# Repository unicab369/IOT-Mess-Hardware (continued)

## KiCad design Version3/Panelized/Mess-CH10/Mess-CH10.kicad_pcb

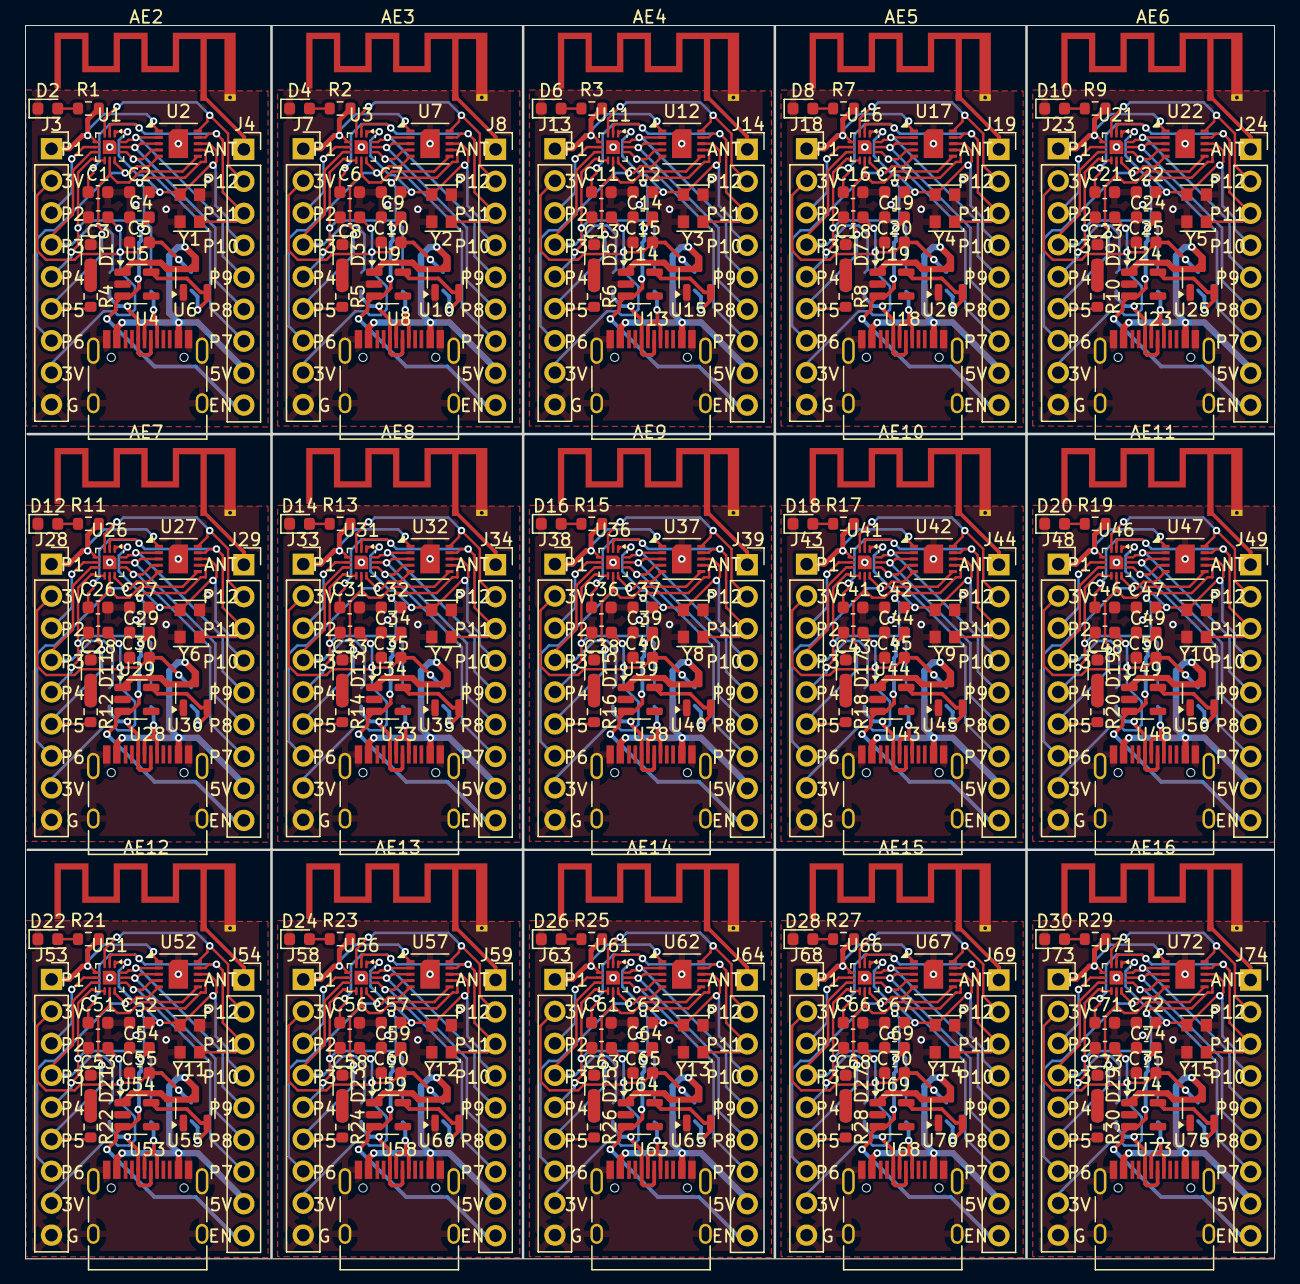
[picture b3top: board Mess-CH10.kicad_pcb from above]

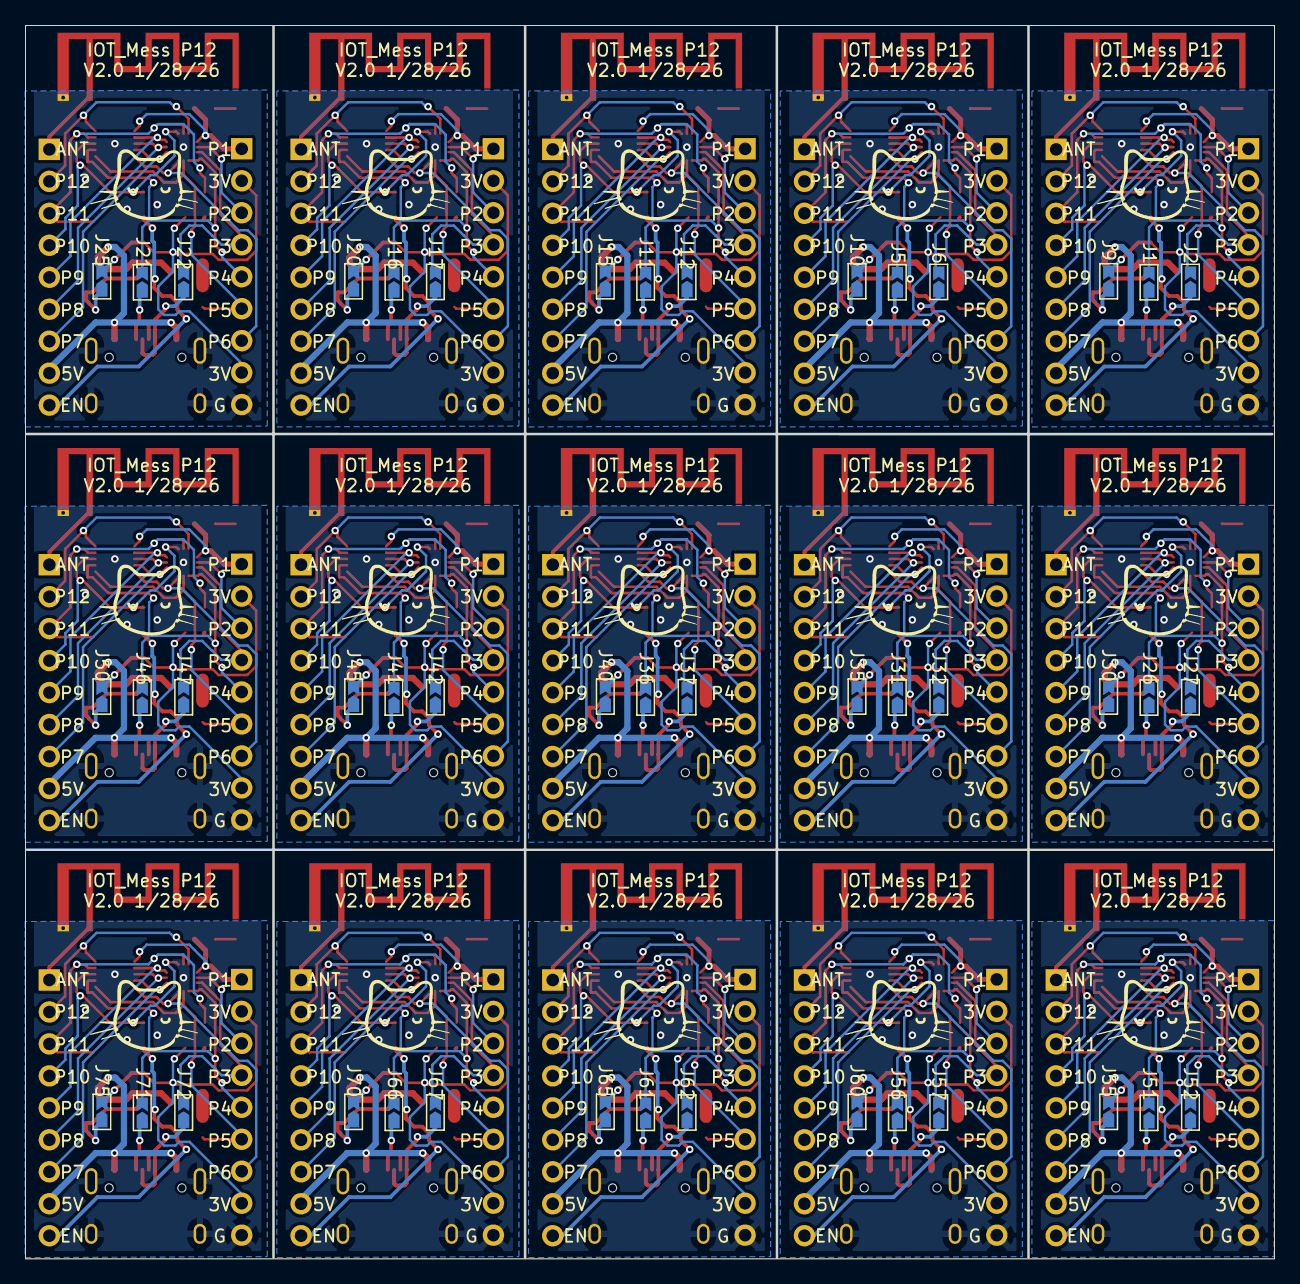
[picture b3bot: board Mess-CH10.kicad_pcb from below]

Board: 2 copper layers, 99.2 x 98.0 mm, 315 parts (45 on the bottom side), 22 nets.

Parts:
AE2, AE3, AE4, AE5, AE6, AE7, AE8, AE9, AE10, AE11, AE12, AE13, AE14, AE15, AE16: Antenna_Shield; Texas_SWRA117D_2.4GHz_Left
C1, C2, C6, C7, C11, C12, C16, C17, C21, C22, C26, C27, C31, C32, C36, C37, C41, C42, C46, C47, C51, C52, C56, C57, C61, C62, C66, C67, C71, C72: 12-25pF; C_0603_1608Metric
C3, C8, C13, C18, C23, C28, C33, C38, C43, C48, C53, C58, C63, C68, C73: 10u; C_0603_1608Metric
C4, C5, C9, C10, C14, C15, C19, C20, C24, C25, C29, C30, C34, C35, C39, C40, C44, C45, C49, C50, C54, C55, C59, C60, C64, C65, C69, C70, C74, C75: 1u; C_0603_1608Metric
D1, D2, D3, D4, D5, D6, D7, D8, D9, D10, D11, D12, D13, D14, D15, D16, D17, D18, D19, D20, D21, D22, D23, D24, D25, D26, D27, D28, D29, D30: LED; LED_0603_1608Metric
J1, J2, J5, J6, J9, J10, J11, J12, J15, J16, J17, J20, J21, J22, J25, J26, J27, J30, J31, J32, J35, J36, J37, J40, J41, J42, J45, J46, J47, J50, J51, J52, J55, J56, J57, J60, J61, J62, J65, J66, J67, J70, J71, J72, J75: Jumper_2; Jumper-triangle
J3, J4, J7, J8, J13, J14, J18, J19, J23, J24, J28, J29, J33, J34, J38, J39, J43, J44, J48, J49, J53, J54, J58, J59, J63, J64, J68, J69, J73, J74: Conn_01x09_Pin; PinSocket_1x09_P2.54mm_Vertical
R1, R2, R3, R4, R5, R6, R7, R8, R9, R10, R11, R12, R13, R14, R15, R16, R17, R18, R19, R20, R21, R22, R23, R24, R25, R26, R27, R28, R29, R30: R; R_0603_1608Metric
U1, U3, U11, U16, U21, U26, U31, U36, U41, U46, U51, U56, U61, U66, U71: UQFN-12-1EP_2x2mm_P0.4mm_EP1.1x1.1mm
U2, U7, U12, U17, U22, U27, U32, U37, U42, U47, U52, U57, U62, U67, U72: CH57xQ_QFN10x3; DFN10x3
U4, U8, U13, U18, U23, U28, U33, U38, U43, U48, U53, U58, U63, U68, U73: USB_C_Receptacle_USB2.0_16P; USB_C_Receptacle_HRO_TYPE-C-31-M-12
U5, U9, U14, U19, U24, U29, U34, U39, U44, U49, U54, U59, U64, U69, U74: ME6211C33M5; SOT-23-5
U6, U10, U15, U20, U25, U30, U35, U40, U45, U50, U55, U60, U65, U70, U75: XC6206PxxxMR; SOT-23-3
Y1, Y2, Y3, Y4, Y5, Y6, Y7, Y8, Y9, Y10, Y11, Y12, Y13, Y14, Y15: XO32; Oscillator_SMD_EuroQuartz_XO32-4Pin_3.2x2.5mm

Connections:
5V: J4.8, J8.8, J14.8, J19.8, J24.8, J29.8, J34.8, J39.8, J44.8, J49.8, J54.8, J59.8, J64.8, J69.8, J74.8, U4.A4 (VBUS), U4.A9 (VBUS), U4.B4 (VBUS), U4.B9 (VBUS), U5.1 (V_{IN}), U6.3 (VI), U8.A4 (VBUS), U8.A9 (VBUS), U8.B4 (VBUS), U8.B9 (VBUS), U9.1 (V_{IN}), U10.3 (VI), U13.A4 (VBUS), U13.A9 (VBUS), U13.B4 (VBUS), U13.B9 (VBUS), U14.1 (V_{IN}), U15.3 (VI), U18.A4 (VBUS), U18.A9 (VBUS), U18.B4 (VBUS), U18.B9 (VBUS), U19.1 (V_{IN}), U20.3 (VI), U23.A4 (VBUS), U23.A9 (VBUS), U23.B4 (VBUS), U23.B9 (VBUS), U24.1 (V_{IN}), U25.3 (VI), U28.A4 (VBUS), U28.A9 (VBUS), U28.B4 (VBUS), U28.B9 (VBUS), U29.1 (V_{IN}), U30.3 (VI), U33.A4 (VBUS), U33.A9 (VBUS), U33.B4 (VBUS), U33.B9 (VBUS), U34.1 (V_{IN}), U35.3 (VI), U38.A4 (VBUS), U38.A9 (VBUS), U38.B4 (VBUS), U38.B9 (VBUS), U39.1 (V_{IN}), U40.3 (VI), U43.A4 (VBUS), U43.A9 (VBUS), U43.B4 (VBUS), U43.B9 (VBUS), U44.1 (V_{IN}), U45.3 (VI), U48.A4 (VBUS), U48.A9 (VBUS), U48.B4 (VBUS), U48.B9 (VBUS), U49.1 (V_{IN}), U50.3 (VI), U53.A4 (VBUS), U53.A9 (VBUS), U53.B4 (VBUS), U53.B9 (VBUS), U54.1 (V_{IN}), U55.3 (VI), U58.A4 (VBUS), U58.A9 (VBUS), U58.B4 (VBUS), U58.B9 (VBUS), U59.1 (V_{IN}), U60.3 (VI), U63.A4 (VBUS), U63.A9 (VBUS), U63.B4 (VBUS), U63.B9 (VBUS), U64.1 (V_{IN}), U65.3 (VI), U68.A4 (VBUS), U68.A9 (VBUS), U68.B4 (VBUS), U68.B9 (VBUS), U69.1 (V_{IN}), U70.3 (VI), U73.A4 (VBUS), U73.A9 (VBUS), U73.B4 (VBUS), U73.B9 (VBUS), U74.1 (V_{IN}), U75.3 (VI)
+3.3V: C3.1, C5.1, C8.1, C10.1, C13.1, C15.1, C18.1, C20.1, C23.1, C25.1, C28.1, C30.1, C33.1, C35.1, C38.1, C40.1, C43.1, C45.1, C48.1, C50.1, C53.1, C55.1, C58.1, C60.1, C63.1, C65.1, C68.1, C70.1, C73.1, C75.1, J3.2, J3.8, J7.2, J7.8, J9.2 (B), J10.2 (B), J13.2, J13.8, J15.2 (B), J18.2, J18.8, J20.2 (B), J23.2, J23.8, J25.2 (B), J28.2, J28.8, J30.2 (B), J33.2, J33.8, J35.2 (B), J38.2, J38.8, J40.2 (B), J43.2, J43.8, J45.2 (B), J48.2, J48.8, J50.2 (B), J53.2, J53.8, J55.2 (B), J58.2, J58.8, J60.2 (B), J63.2, J63.8, J65.2 (B), J68.2, J68.8, J70.2 (B), J73.2, J73.8, J75.2 (B)
D+: J1.1 (A), J5.1 (A), J11.1 (A), J16.1 (A), J21.1 (A), J26.1 (A), J31.1 (A), J36.1 (A), J41.1 (A), J46.1 (A), J51.1 (A), J56.1 (A), J61.1 (A), J66.1 (A), J71.1 (A), U4.A6 (D+), U4.B6 (D+), U8.A6 (D+), U8.B6 (D+), U13.A6 (D+), U13.B6 (D+), U18.A6 (D+), U18.B6 (D+), U23.A6 (D+), U23.B6 (D+), U28.A6 (D+), U28.B6 (D+), U33.A6 (D+), U33.B6 (D+), U38.A6 (D+), U38.B6 (D+), U43.A6 (D+), U43.B6 (D+), U48.A6 (D+), U48.B6 (D+), U53.A6 (D+), U53.B6 (D+), U58.A6 (D+), U58.B6 (D+), U63.A6 (D+), U63.B6 (D+), U68.A6 (D+), U68.B6 (D+), U73.A6 (D+), U73.B6 (D+)
D-: J2.1 (A), J6.1 (A), J12.1 (A), J17.1 (A), J22.1 (A), J27.1 (A), J32.1 (A), J37.1 (A), J42.1 (A), J47.1 (A), J52.1 (A), J57.1 (A), J62.1 (A), J67.1 (A), J72.1 (A), U4.A7 (D-), U4.B7 (D-), U8.A7 (D-), U8.B7 (D-), U13.A7 (D-), U13.B7 (D-), U18.A7 (D-), U18.B7 (D-), U23.A7 (D-), U23.B7 (D-), U28.A7 (D-), U28.B7 (D-), U33.A7 (D-), U33.B7 (D-), U38.A7 (D-), U38.B7 (D-), U43.A7 (D-), U43.B7 (D-), U48.A7 (D-), U48.B7 (D-), U53.A7 (D-), U53.B7 (D-), U58.A7 (D-), U58.B7 (D-), U63.A7 (D-), U63.B7 (D-), U68.A7 (D-), U68.B7 (D-), U73.A7 (D-), U73.B7 (D-)
GND: AE2.2 (Shield), AE3.2 (Shield), AE4.2 (Shield), AE5.2 (Shield), AE6.2 (Shield), AE7.2 (Shield), AE8.2 (Shield), AE9.2 (Shield), AE10.2 (Shield), AE11.2 (Shield), AE12.2 (Shield), AE13.2 (Shield), AE14.2 (Shield), AE15.2 (Shield), AE16.2 (Shield), C1.2, C2.2, C3.2, C4.2, C5.2, C6.2, C7.2, C8.2, C9.2, C10.2, C11.2, C12.2, C13.2, C14.2, C15.2, C16.2, C17.2, C18.2, C19.2, C20.2, C21.2, C22.2, C23.2, C24.2, C25.2, C26.2, C27.2, C28.2, C29.2, C30.2, C31.2, C32.2, C33.2, C34.2, C35.2, C36.2, C37.2, C38.2, C39.2, C40.2, C41.2, C42.2, C43.2, C44.2, C45.2, C46.2, C47.2, C48.2, C49.2, C50.2, C51.2, C52.2, C53.2, C54.2, C55.2, C56.2, C57.2, C58.2, C59.2, C60.2, C61.2, C62.2, C63.2, C64.2, C65.2, C66.2, C67.2, C68.2, C69.2, C70.2, C71.2, C72.2, C73.2, C74.2, C75.2, D1.1 (K), D2.1 (K), D3.1 (K), D4.1 (K), D5.1 (K), D6.1 (K), D7.1 (K), D8.1 (K), D9.1 (K), D10.1 (K), D11.1 (K), D12.1 (K), D13.1 (K), D14.1 (K), D15.1 (K), D16.1 (K), D17.1 (K), D18.1 (K), D19.1 (K), D20.1 (K), D21.1 (K), D22.1 (K), D23.1 (K), D24.1 (K), D25.1 (K), D26.1 (K), D27.1 (K), D28.1 (K), D29.1 (K), D30.1 (K), J3.9, J7.9, J13.9, J18.9, J23.9, J28.9, J33.9, J38.9, J43.9, J48.9, J53.9, J58.9, J63.9, J68.9, J73.9, U1.13 (GND), U2.11 (GND), U3.13 (GND), U4.A1 (GND), U4.A12 (GND), U4.B1 (GND), U4.B12 (GND), U4.S1 (SHIELD), U5.2 (V_{SS}), U6.1 (GND), U7.11 (GND), U8.A1 (GND), U8.A12 (GND), U8.B1 (GND), U8.B12 (GND), U8.S1 (SHIELD), U9.2 (V_{SS}), U10.1 (GND), U11.13 (GND), U12.11 (GND), U13.A1 (GND), U13.A12 (GND), U13.B1 (GND), U13.B12 (GND), U13.S1 (SHIELD), U14.2 (V_{SS}), U15.1 (GND), U16.13 (GND), U17.11 (GND), U18.A1 (GND), U18.A12 (GND), U18.B1 (GND), U18.B12 (GND), U18.S1 (SHIELD), U19.2 (V_{SS}), U20.1 (GND), U21.13 (GND), U22.11 (GND), U23.A1 (GND), U23.A12 (GND), U23.B1 (GND), U23.B12 (GND), U23.S1 (SHIELD), U24.2 (V_{SS}), U25.1 (GND), U26.13 (GND), U27.11 (GND), U28.A1 (GND), U28.A12 (GND), U28.B1 (GND), U28.B12 (GND), U28.S1 (SHIELD), U29.2 (V_{SS}), U30.1 (GND), U31.13 (GND), U32.11 (GND), U33.A1 (GND), U33.A12 (GND), U33.B1 (GND), U33.B12 (GND), U33.S1 (SHIELD), U34.2 (V_{SS}), U35.1 (GND), U36.13 (GND), U37.11 (GND), U38.A1 (GND), U38.A12 (GND), U38.B1 (GND), U38.B12 (GND), U38.S1 (SHIELD), U39.2 (V_{SS}), U40.1 (GND), U41.13 (GND), U42.11 (GND), U43.A1 (GND), U43.A12 (GND), U43.B1 (GND), U43.B12 (GND), U43.S1 (SHIELD), U44.2 (V_{SS}), U45.1 (GND), U46.13 (GND), U47.11 (GND), U48.A1 (GND), U48.A12 (GND), U48.B1 (GND), U48.B12 (GND), U48.S1 (SHIELD), U49.2 (V_{SS}), U50.1 (GND), U51.13 (GND), U52.11 (GND), U53.A1 (GND), U53.A12 (GND), U53.B1 (GND), U53.B12 (GND), U53.S1 (SHIELD), U54.2 (V_{SS}), U55.1 (GND), U56.13 (GND), U57.11 (GND), U58.A1 (GND), U58.A12 (GND), U58.B1 (GND), U58.B12 (GND), U58.S1 (SHIELD), U59.2 (V_{SS}), U60.1 (GND), U61.13 (GND), U62.11 (GND), U63.A1 (GND), U63.A12 (GND), U63.B1 (GND), U63.B12 (GND), U63.S1 (SHIELD), U64.2 (V_{SS}), U65.1 (GND), U66.13 (GND), U67.11 (GND), U68.A1 (GND), U68.A12 (GND), U68.B1 (GND), U68.B12 (GND), U68.S1 (SHIELD), U69.2 (V_{SS}), U70.1 (GND), U71.13 (GND), U72.11 (GND), U73.A1 (GND), U73.A12 (GND), U73.B1 (GND), U73.B12 (GND), U73.S1 (SHIELD), U74.2 (V_{SS}), U75.1 (GND), Y1.2 (GND), Y1.4 (GND), Y2.2 (GND), Y2.4 (GND), Y3.2 (GND), Y3.4 (GND), Y4.2 (GND), Y4.4 (GND), Y5.2 (GND), Y5.4 (GND), Y6.2 (GND), Y6.4 (GND), Y7.2 (GND), Y7.4 (GND), Y8.2 (GND), Y8.4 (GND), Y9.2 (GND), Y9.4 (GND), Y10.2 (GND), Y10.4 (GND), Y11.2 (GND), Y11.4 (GND), Y12.2 (GND), Y12.4 (GND), Y13.2 (GND), Y13.4 (GND), Y14.2 (GND), Y14.4 (GND), Y15.2 (GND), Y15.4 (GND)
LDO_EN: C4.1, C9.1, C14.1, C19.1, C24.1, C29.1, C34.1, C39.1, C44.1, C49.1, C54.1, C59.1, C64.1, C69.1, C74.1, J4.9, J8.9, J14.9, J19.9, J24.9, J29.9, J34.9, J39.9, J44.9, J49.9, J54.9, J59.9, J64.9, J69.9, J74.9, U5.3 (CE), U9.3 (CE), U14.3 (CE), U19.3 (CE), U24.3 (CE), U29.3 (CE), U34.3 (CE), U39.3 (CE), U44.3 (CE), U49.3 (CE), U54.3 (CE), U59.3 (CE), U64.3 (CE), U69.3 (CE), U74.3 (CE)
unnamed: AE2.1 (A), AE3.1 (A), AE4.1 (A), AE5.1 (A), AE6.1 (A), AE7.1 (A), AE8.1 (A), AE9.1 (A), AE10.1 (A), AE11.1 (A), AE12.1 (A), AE13.1 (A), AE14.1 (A), AE15.1 (A), AE16.1 (A), J4.1, J8.1, J14.1, J19.1, J24.1, J29.1, J34.1, J39.1, J44.1, J49.1, J54.1, J59.1, J64.1, J69.1, J74.1
unnamed: D1.2 (A), D3.2 (A), D5.2 (A), D7.2 (A), D9.2 (A), D11.2 (A), D13.2 (A), D15.2 (A), D17.2 (A), D19.2 (A), D21.2 (A), D23.2 (A), D25.2 (A), D27.2 (A), D29.2 (A), R4.2, R5.2, R6.2, R8.2, R10.2, R12.2, R14.2, R16.2, R18.2, R20.2, R22.2, R24.2, R26.2, R28.2, R30.2
unnamed: D2.2 (A), D4.2 (A), D6.2 (A), D8.2 (A), D10.2 (A), D12.2 (A), D14.2 (A), D16.2 (A), D18.2 (A), D20.2 (A), D22.2 (A), D24.2 (A), D26.2 (A), D28.2 (A), D30.2 (A), R1.2, R2.2, R3.2, R7.2, R9.2, R11.2, R13.2, R15.2, R17.2, R19.2, R21.2, R23.2, R25.2, R27.2, R29.2
unnamed: J9.1 (A), J10.1 (A), J15.1 (A), J20.1 (A), J25.1 (A), J30.1 (A), J35.1 (A), J40.1 (A), J45.1 (A), J50.1 (A), J55.1 (A), J60.1 (A), J65.1 (A), J70.1 (A), J75.1 (A), U5.5 (V_{OUT}), U6.2 (VO), U9.5 (V_{OUT}), U10.2 (VO), U14.5 (V_{OUT}), U15.2 (VO), U19.5 (V_{OUT}), U20.2 (VO), U24.5 (V_{OUT}), U25.2 (VO), U29.5 (V_{OUT}), U30.2 (VO), U34.5 (V_{OUT}), U35.2 (VO), U39.5 (V_{OUT}), U40.2 (VO), U44.5 (V_{OUT}), U45.2 (VO), U49.5 (V_{OUT}), U50.2 (VO), U54.5 (V_{OUT}), U55.2 (VO), U59.5 (V_{OUT}), U60.2 (VO), U64.5 (V_{OUT}), U65.2 (VO), U69.5 (V_{OUT}), U70.2 (VO), U74.5 (V_{OUT}), U75.2 (VO)
P_1: J3.1, J7.1, J13.1, J18.1, J23.1, J28.1, J33.1, J38.1, J43.1, J48.1, J53.1, J58.1, J63.1, J68.1, J73.1, R1.1, R2.1, R3.1, R7.1, R9.1, R11.1, R13.1, R15.1, R17.1, R19.1, R21.1, R23.1, R25.1, R27.1, R29.1, U1.4 (VDD), U2.1 (VDD), U3.4 (VDD), U7.1 (VDD), U11.4 (VDD), U12.1 (VDD), U16.4 (VDD), U17.1 (VDD), U21.4 (VDD), U22.1 (VDD), U26.4 (VDD), U27.1 (VDD), U31.4 (VDD), U32.1 (VDD), U36.4 (VDD), U37.1 (VDD), U41.4 (VDD), U42.1 (VDD), U46.4 (VDD), U47.1 (VDD), U51.4 (VDD), U52.1 (VDD), U56.4 (VDD), U57.1 (VDD), U61.4 (VDD), U62.1 (VDD), U66.4 (VDD), U67.1 (VDD), U71.4 (VDD), U72.1 (VDD)
P_2: J3.3, J7.3, J13.3, J18.3, J23.3, J28.3, J33.3, J38.3, J43.3, J48.3, J53.3, J58.3, J63.3, J68.3, J73.3, U1.5 (PC0), U3.5 (PC0), U11.5 (PC0), U16.5 (PC0), U21.5 (PC0), U26.5 (PC0), U31.5 (PC0), U36.5 (PC0), U41.5 (PC0), U46.5 (PC0), U51.5 (PC0), U56.5 (PC0), U61.5 (PC0), U66.5 (PC0), U71.5 (PC0)
P_3: J2.2 (B), J3.4, J6.2 (B), J7.4, J12.2 (B), J13.4, J17.2 (B), J18.4, J22.2 (B), J23.4, J27.2 (B), J28.4, J32.2 (B), J33.4, J37.2 (B), J38.4, J42.2 (B), J43.4, J47.2 (B), J48.4, J52.2 (B), J53.4, J57.2 (B), J58.4, J62.2 (B), J63.4, J67.2 (B), J68.4, J72.2 (B), J73.4, U1.6 (PC3), U3.6 (PC3), U11.6 (PC3), U16.6 (PC3), U21.6 (PC3), U26.6 (PC3), U31.6 (PC3), U36.6 (PC3), U41.6 (PC3), U46.6 (PC3), U51.6 (PC3), U56.6 (PC3), U61.6 (PC3), U66.6 (PC3), U71.6 (PC3)
P_4: J1.2 (B), J3.5, J5.2 (B), J7.5, J11.2 (B), J13.5, J16.2 (B), J18.5, J21.2 (B), J23.5, J26.2 (B), J28.5, J31.2 (B), J33.5, J36.2 (B), J38.5, J41.2 (B), J43.5, J46.2 (B), J48.5, J51.2 (B), J53.5, J56.2 (B), J58.5, J61.2 (B), J63.5, J66.2 (B), J68.5, J71.2 (B), J73.5, U1.7 (PC4/MCO/A2), U2.7 (PA3/SCL2), U3.7 (PC4/MCO/A2), U7.7 (PA3/SCL2), U11.7 (PC4/MCO/A2), U12.7 (PA3/SCL2), U16.7 (PC4/MCO/A2), U17.7 (PA3/SCL2), U21.7 (PC4/MCO/A2), U22.7 (PA3/SCL2), U26.7 (PC4/MCO/A2), U27.7 (PA3/SCL2), U31.7 (PC4/MCO/A2), U32.7 (PA3/SCL2), U36.7 (PC4/MCO/A2), U37.7 (PA3/SCL2), U41.7 (PC4/MCO/A2), U42.7 (PA3/SCL2), U46.7 (PC4/MCO/A2), U47.7 (PA3/SCL2), U51.7 (PC4/MCO/A2), U52.7 (PA3/SCL2), U56.7 (PC4/MCO/A2), U57.7 (PA3/SCL2), U61.7 (PC4/MCO/A2), U62.7 (PA3/SCL2), U66.7 (PC4/MCO/A2), U67.7 (PA3/SCL2), U71.7 (PC4/MCO/A2), U72.7 (PA3/SCL2)
P_5: J3.6, J7.6, J13.6, J18.6, J23.6, J28.6, J33.6, J38.6, J43.6, J48.6, J53.6, J58.6, J63.6, J68.6, J73.6, R4.1, R5.1, R6.1, R8.1, R10.1, R12.1, R14.1, R16.1, R18.1, R20.1, R22.1, R24.1, R26.1, R28.1, R30.1, U1.8 (PC6), U2.6 (PA2/SDA2), U3.8 (PC6), U7.6 (PA2/SDA2), U11.8 (PC6), U12.6 (PA2/SDA2), U16.8 (PC6), U17.6 (PA2/SDA2), U21.8 (PC6), U22.6 (PA2/SDA2), U26.8 (PC6), U27.6 (PA2/SDA2), U31.8 (PC6), U32.6 (PA2/SDA2), U36.8 (PC6), U37.6 (PA2/SDA2), U41.8 (PC6), U42.6 (PA2/SDA2), U46.8 (PC6), U47.6 (PA2/SDA2), U51.8 (PC6), U52.6 (PA2/SDA2), U56.8 (PC6), U57.6 (PA2/SDA2), U61.8 (PC6), U62.6 (PA2/SDA2), U66.8 (PC6), U67.6 (PA2/SDA2), U71.8 (PC6), U72.6 (PA2/SDA2)
P_6: J3.7, J7.7, J13.7, J18.7, J23.7, J28.7, J33.7, J38.7, J43.7, J48.7, J53.7, J58.7, J63.7, J68.7, J73.7, U1.9 (PC7), U2.5 (PA7/TMR), U3.9 (PC7), U7.5 (PA7/TMR), U11.9 (PC7), U12.5 (PA7/TMR), U16.9 (PC7), U17.5 (PA7/TMR), U21.9 (PC7), U22.5 (PA7/TMR), U26.9 (PC7), U27.5 (PA7/TMR), U31.9 (PC7), U32.5 (PA7/TMR), U36.9 (PC7), U37.5 (PA7/TMR), U41.9 (PC7), U42.5 (PA7/TMR), U46.9 (PC7), U47.5 (PA7/TMR), U51.9 (PC7), U52.5 (PA7/TMR), U56.9 (PC7), U57.5 (PA7/TMR), U61.9 (PC7), U62.5 (PA7/TMR), U66.9 (PC7), U67.5 (PA7/TMR), U71.9 (PC7), U72.5 (PA7/TMR)
P_7: J4.7, J8.7, J14.7, J19.7, J24.7, J29.7, J34.7, J39.7, J44.7, J49.7, J54.7, J59.7, J64.7, J69.7, J74.7, U1.10 (PD1/SWIO/SCL_/RX_), U2.4 (PA1/UDP/SDA1), U3.10 (PD1/SWIO/SCL_/RX_), U7.4 (PA1/UDP/SDA1), U11.10 (PD1/SWIO/SCL_/RX_), U12.4 (PA1/UDP/SDA1), U16.10 (PD1/SWIO/SCL_/RX_), U17.4 (PA1/UDP/SDA1), U21.10 (PD1/SWIO/SCL_/RX_), U22.4 (PA1/UDP/SDA1), U26.10 (PD1/SWIO/SCL_/RX_), U27.4 (PA1/UDP/SDA1), U31.10 (PD1/SWIO/SCL_/RX_), U32.4 (PA1/UDP/SDA1), U36.10 (PD1/SWIO/SCL_/RX_), U37.4 (PA1/UDP/SDA1), U41.10 (PD1/SWIO/SCL_/RX_), U42.4 (PA1/UDP/SDA1), U46.10 (PD1/SWIO/SCL_/RX_), U47.4 (PA1/UDP/SDA1), U51.10 (PD1/SWIO/SCL_/RX_), U52.4 (PA1/UDP/SDA1), U56.10 (PD1/SWIO/SCL_/RX_), U57.4 (PA1/UDP/SDA1), U61.10 (PD1/SWIO/SCL_/RX_), U62.4 (PA1/UDP/SDA1), U66.10 (PD1/SWIO/SCL_/RX_), U67.4 (PA1/UDP/SDA1), U71.10 (PD1/SWIO/SCL_/RX_), U72.4 (PA1/UDP/SDA1)
P_8: J4.6, J8.6, J14.6, J19.6, J24.6, J29.6, J34.6, J39.6, J44.6, J49.6, J54.6, J59.6, J64.6, J69.6, J74.6, U1.11 (PD4/A7), U2.3 (PA0/UDM/SCL1), U3.11 (PD4/A7), U7.3 (PA0/UDM/SCL1), U11.11 (PD4/A7), U12.3 (PA0/UDM/SCL1), U16.11 (PD4/A7), U17.3 (PA0/UDM/SCL1), U21.11 (PD4/A7), U22.3 (PA0/UDM/SCL1), U26.11 (PD4/A7), U27.3 (PA0/UDM/SCL1), U31.11 (PD4/A7), U32.3 (PA0/UDM/SCL1), U36.11 (PD4/A7), U37.3 (PA0/UDM/SCL1), U41.11 (PD4/A7), U42.3 (PA0/UDM/SCL1), U46.11 (PD4/A7), U47.3 (PA0/UDM/SCL1), U51.11 (PD4/A7), U52.3 (PA0/UDM/SCL1), U56.11 (PD4/A7), U57.3 (PA0/UDM/SCL1), U61.11 (PD4/A7), U62.3 (PA0/UDM/SCL1), U66.11 (PD4/A7), U67.3 (PA0/UDM/SCL1), U71.11 (PD4/A7), U72.3 (PA0/UDM/SCL1)
P_9: J4.5, J8.5, J14.5, J19.5, J24.5, J29.5, J34.5, J39.5, J44.5, J49.5, J54.5, J59.5, J64.5, J69.5, J74.5, U1.12 (PD7/RST/PA4), U2.2 (V5), U3.12 (PD7/RST/PA4), U7.2 (V5), U11.12 (PD7/RST/PA4), U12.2 (V5), U16.12 (PD7/RST/PA4), U17.2 (V5), U21.12 (PD7/RST/PA4), U22.2 (V5), U26.12 (PD7/RST/PA4), U27.2 (V5), U31.12 (PD7/RST/PA4), U32.2 (V5), U36.12 (PD7/RST/PA4), U37.2 (V5), U41.12 (PD7/RST/PA4), U42.2 (V5), U46.12 (PD7/RST/PA4), U47.2 (V5), U51.12 (PD7/RST/PA4), U52.2 (V5), U56.12 (PD7/RST/PA4), U57.2 (V5), U61.12 (PD7/RST/PA4), U62.2 (V5), U66.12 (PD7/RST/PA4), U67.2 (V5), U71.12 (PD7/RST/PA4), U72.2 (V5)
P_10: C2.1, C7.1, C12.1, C17.1, C22.1, C27.1, C32.1, C37.1, C42.1, C47.1, C52.1, C57.1, C62.1, C67.1, C72.1, J4.4, J8.4, J14.4, J19.4, J24.4, J29.4, J34.4, J39.4, J44.4, J49.4, J54.4, J59.4, J64.4, J69.4, J74.4, U1.1 (PA1/XI), U2.8 (X0), U3.1 (PA1/XI), U7.8 (X0), U11.1 (PA1/XI), U12.8 (X0), U16.1 (PA1/XI), U17.8 (X0), U21.1 (PA1/XI), U22.8 (X0), U26.1 (PA1/XI), U27.8 (X0), U31.1 (PA1/XI), U32.8 (X0), U36.1 (PA1/XI), U37.8 (X0), U41.1 (PA1/XI), U42.8 (X0), U46.1 (PA1/XI), U47.8 (X0), U51.1 (PA1/XI), U52.8 (X0), U56.1 (PA1/XI), U57.8 (X0), U61.1 (PA1/XI), U62.8 (X0), U66.1 (PA1/XI), U67.8 (X0), U71.1 (PA1/XI), U72.8 (X0), Y1.3 (XO), Y2.3 (XO), Y3.3 (XO), Y4.3 (XO), Y5.3 (XO), Y6.3 (XO), Y7.3 (XO), Y8.3 (XO), Y9.3 (XO), Y10.3 (XO), Y11.3 (XO), Y12.3 (XO), Y13.3 (XO), Y14.3 (XO), Y15.3 (XO)
P_11: C1.1, C6.1, C11.1, C16.1, C21.1, C26.1, C31.1, C36.1, C41.1, C46.1, C51.1, C56.1, C61.1, C66.1, C71.1, J4.3, J8.3, J14.3, J19.3, J24.3, J29.3, J34.3, J39.3, J44.3, J49.3, J54.3, J59.3, J64.3, J69.3, J74.3, U1.2 (PA2/X0), U2.9 (XI), U3.2 (PA2/X0), U7.9 (XI), U11.2 (PA2/X0), U12.9 (XI), U16.2 (PA2/X0), U17.9 (XI), U21.2 (PA2/X0), U22.9 (XI), U26.2 (PA2/X0), U27.9 (XI), U31.2 (PA2/X0), U32.9 (XI), U36.2 (PA2/X0), U37.9 (XI), U41.2 (PA2/X0), U42.9 (XI), U46.2 (PA2/X0), U47.9 (XI), U51.2 (PA2/X0), U52.9 (XI), U56.2 (PA2/X0), U57.9 (XI), U61.2 (PA2/X0), U62.9 (XI), U66.2 (PA2/X0), U67.9 (XI), U71.2 (PA2/X0), U72.9 (XI), Y1.1 (XI), Y2.1 (XI), Y3.1 (XI), Y4.1 (XI), Y5.1 (XI), Y6.1 (XI), Y7.1 (XI), Y8.1 (XI), Y9.1 (XI), Y10.1 (XI), Y11.1 (XI), Y12.1 (XI), Y13.1 (XI), Y14.1 (XI), Y15.1 (XI)
P_12: J4.2, J8.2, J14.2, J19.2, J24.2, J29.2, J34.2, J39.2, J44.2, J49.2, J54.2, J59.2, J64.2, J69.2, J74.2, U1.3 (PD0/SDA_/TX_), U2.10 (ANT), U3.3 (PD0/SDA_/TX_), U7.10 (ANT), U11.3 (PD0/SDA_/TX_), U12.10 (ANT), U16.3 (PD0/SDA_/TX_), U17.10 (ANT), U21.3 (PD0/SDA_/TX_), U22.10 (ANT), U26.3 (PD0/SDA_/TX_), U27.10 (ANT), U31.3 (PD0/SDA_/TX_), U32.10 (ANT), U36.3 (PD0/SDA_/TX_), U37.10 (ANT), U41.3 (PD0/SDA_/TX_), U42.10 (ANT), U46.3 (PD0/SDA_/TX_), U47.10 (ANT), U51.3 (PD0/SDA_/TX_), U52.10 (ANT), U56.3 (PD0/SDA_/TX_), U57.10 (ANT), U61.3 (PD0/SDA_/TX_), U62.10 (ANT), U66.3 (PD0/SDA_/TX_), U67.10 (ANT), U71.3 (PD0/SDA_/TX_), U72.10 (ANT)
